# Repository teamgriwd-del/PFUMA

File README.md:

# PFUMA/INGCEBO - Enterprise Agri-Health Intelligence

*pfuma* — the Shona word for wealth. For a rural family, that wealth is standing in the kraal. PFUMA/INGCEBO is the system that protects it.

PFUMA/INGCEBO is a comprehensive, enterprise-grade livestock health and management platform specifically tailored for Zimbabwean farmers and veterinarians. Built for the Zimbabwe Agricultural Show, it provides digital tools to enhance productivity, automate health compliance, and provide rapid emergency response.

## 📊 The Problem

Livestock is often a rural family's largest store of wealth. It is also the least protected asset they own.

- **500,000+** cattle lost to disease (Theileriosis / "January Disease") since 2016 — most of it preventable if caught early.
- **3,400+** arrests in a single stock-theft crackdown operation.
- **0** verifiable digital records — police can't clear a sale they have no visibility into, and a buyer can't check a story he's only been told.
- **Paper trail, not a real one.** Ownership, health history, vaccination records and past sales are tracked on paper, by memory, or not at all — a record that can be lost, forged, or simply never existed in the first place.
- **No way to verify livestock history.** A buyer has no way to confirm an animal's health record, vaccination status, or true ownership before paying — they're trusting a stranger's word, not a record.
- **Ownership disputes with no evidence.** If a cow is stolen or its ownership is disputed, a farmer has no fast, credible way to prove it's really his.
- **Informal, undocumented sales channels.** Farmers relying on word-of-mouth buyers get lowballed with no visibility into fair market price, and have no documented sale history to fall back on.
- **Livestock wealth is illiquid.** Without verified ownership and health records, that wealth is hard to use as proof of value when a farmer needs credit.

The gap isn't goodwill — it's proof.

## 👑 The PFUMA/INGCEBO Experience

### 1. Jinda: The AI Farm Assistant
A state-of-the-art AI assistant trained on a vast knowledge base of Zimbabwean livestock protocols.
- **NLP Engine:** Handles natural language queries from non-technical users.
- **Smart Navigation:** Responds to commands like "Take me to the marketplace" or "Take me home."
- **Deep Knowledge:** Trained on January Disease (Theileriosis), Anthrax, and Cattle Gestation/Weaning standards.
- **Herd Analytics:** Instantly calculates herd size and health trends via chat.

### 2. Enterprise Diagnostics (Weighted Engine)
Advanced diagnostic system with weighted symptom matching.
- **Weighted Logic:** Differentiates between Primary and Secondary symptoms.
- **Action Plans:** Provides multi-step procedures for commercial farm management.
- **Zim Focus:** Specific training on regional threats common in Mashonaland, Matabeleland, and Midlands.

### 3. Health & Compliance (Lifecycle Engine)
A full-lifecycle system ensuring commercial compliance.
- **Automated Lifecycle:** Real-time countdowns for weaning and gestation.
- **Digital Audit Log:** Permanent, timestamped records of every vaccination and treatment.
- **Compliance Tracking:** Color-coded status for Overdue, Due Today, and Upcoming tasks.

### 4. Veterinary Advisory Portal
Structured ticketing system localized for Zimbabwe.
- **Regional Surveillance:** Location tagging by Province and District for national disease tracking.
- **Direct Hotlines:** Instant access to Department of Veterinary Services (DVS) regional offices.

### 5. Police Oversight & Sale Clearance
A fifth stakeholder role modelling real-world livestock-trade law enforcement.
- **Signup Verification Queue:** Police review Farmer/Supplier/Buyer applications (Vets are peer-reviewed by an existing verified vet); Police accounts are provisioned out-of-band, not self-service.
- **Sale Clearance Queue:** Every livestock marketplace listing tied to a registered animal starts `pending_clearance` and stays invisible to buyers until an officer verifies ownership/brand papers and issues a movement permit number.
- **Document Verification at Signup:** Every role uploads an ID document plus a role-specific credential (DVS license, business registration, land proof, etc.) — see [`signup-verification-requirements.md`](DOCUMENTATION/compliance-research/signup-verification-requirements.md).

### 6. Compliance Knowledge Base
Researched, cited reference material — not legal advice — covering Zimbabwean livestock law and species-specific health requirements for Cattle, Pigs, Sheep, and Goats. See the [`DOCUMENTATION/compliance-research/`](DOCUMENTATION/compliance-research/) folder. Jinda draws on a condensed version of this to answer "what do I need to legally keep/sell X" questions in-chat.

### 7. Real Authentication & Role-Based Access Control
- **Password auth (bcrypt) + JWT sessions** — no endpoint is open to an unauthenticated caller except health-check, login, register, and public feed reference data.
- **Per-owner data scoping** — a Farmer only ever sees their own animals/health records/inventory; Vets and Police get oversight visibility; the AI companion is role-aware and refuses to discuss another user's data.
- **Uploaded documents** are stored outside the web root and served only to the document's owner or an authorized reviewer.

### 8. Agri Marketplace
Livestock, feed, medicine and equipment listings in one feed.
- **Verified suppliers only** — feed, medicine and vaccine listings come from suppliers vetted at signup.
- **Livestock listings gated by clearance** — an animal-backed listing stays `pending_clearance` and invisible to buyers until police verify ownership/brand papers.
- Buyers see a record, not a stranger's word — the vet's health note and the police clearance travel with the sale.

### 9. PFUMA/INGCEBO Messenger
Direct in-app chat connecting every role — farmers, vets, suppliers and buyers — across Zimbabwe, filterable by role (Vets / Suppliers / Farmers / Buyers) so a farmer can go straight to the DVS officer or supplier they need instead of a phone call and a guess.

### 10. Institutions — Turning Livestock Into Usable Collateral
A sixth stakeholder role for banks and insurers.
- **Certificate Lookup:** An Institution enters a valuation certificate code (issued by a vet for a specific animal) and instantly sees a verified record — identity, health history, estimated market value — instead of taking a borrower's word for what their herd is worth.
- **Collateral/Insurance Flagging:** The Institution can flag a certificate in its own private ledger for loan-collateral or insurance-underwriting purposes, and keeps a running record of every certificate it has looked up.
- This is what makes "livestock wealth is easier to borrow against" (see below) a real, working feature rather than just a talking point.

### 11. Farmer Cooperatives
Farmers can form or join a cooperative to coordinate as a group rather than individually — a shared dip-tank schedule visible to every member, and group vet-consultation requests raised on the cooperative's behalf instead of each farmer messaging separately.

### 12. National Outbreak Reporting
Any Farmer or Veterinarian can report a suspected disease outbreak. A Veterinarian or Admin verifies it, and verification automatically broadcasts a notification to farmers in the affected area — turning informal "have you heard..." warnings into a real, timestamped, region-scoped alert system that feeds the same regional surveillance picture DVS needs for contact tracing.

## 🐄 The Journey of One Animal

| Step | What happens |
|---|---|
| **1. Register** | The farmer records breed, weight, tag ID, brand mark and dip-tank details. No brand on record is flagged as a risk before any sale. |
| **2. Track** | Weight, vaccinations, weaning and gestation run on countdowns. Overdue, due-today and upcoming are colour-coded, not remembered. |
| **3. Treat** | The farmer messages a vet in-app. The vet reviews, treats, and can order medicine from a supplier — three roles, one system. |
| **4. Clear** | The listing opens as `pending_clearance`. An officer verifies ownership and brand papers and issues a movement-permit number. |
| **5. Sell** | Only now can buyers see it. The vet's health record and the police clearance travel with the sale. |

**The headline feature:** the sale cannot go live until an officer clears it. That gate lives in the software, not in a policy document — which is exactly why it doesn't get skipped.

Every registered animal also gets a **Health Passport** — verified digital pedigree and medical record, photos, identity details (name, ear tag, owner brand, breed, age/species), and an **estimated market value** computed from weight, species and health-record history.

## ⚖️ Built on Zimbabwean Law

Every headline feature maps to a specific Act — researched, cited, and in the repo ([`DOCUMENTATION/compliance-research/`](DOCUMENTATION/compliance-research/)) for anyone who wants to check it. This is researched and cited, not a lawyer-certified audit; sources are ZimLII, FAOLEX, CVSZ, Veritas and the Consumer Council, and where a detail couldn't be confirmed, the research says so plainly instead of guessing.

| What PFUMA/INGCEBO enforces | The law it operationalizes |
|---|---|
| Listings start `pending_clearance`; an officer verifies ownership and brand papers and issues a movement-permit number | Stock Theft Prevention Act [9:18] |
| Vet signup requires a CVSZ registration number, peer-reviewed by an already-verified vet | Veterinary Surgeons Act [27:15] |
| Animal records capture brand mark, tag ID and dip-tank; "no brand on record" is flagged before a sale | Brands Act + Livestock Identification Regs |
| Jinda pushes toward DVS or police reporting when a notifiable-disease pattern appears | Animal Health Act [19:01] |
| Cross-district sales prompt for a DVS veterinary movement permit alongside police clearance | The "two-gate" movement process |
| Buyer signup requires acknowledging disclosure, fixed pricing and the statutory right of return | Consumer Protection Act [14:44] |

## 🌾 What This Changes

| For | The change |
|---|---|
| **The Farmer** | Ownership he can prove, disease caught early, and a fair, documented sales channel instead of an isolated lowball offer. Cooperatives let neighbouring farmers coordinate dip-tank schedules and vet requests as a group. |
| **The Veterinarian** | Fewer wasted trips and real outbreak visibility. Province and district tagging, plus the verified outbreak-reporting workflow, builds exactly the regional surveillance data DVS needs for contact tracing. |
| **Suppliers and Buyers** | A direct channel to the farmers who need their stock, and buyers who are no longer one bad purchase away from a receiving-stolen-goods charge. |
| **Police and DVS** | Clearance stops being a paper courtesy and becomes a structural gate. Officers review from a queue instead of chasing paperwork on foot. |
| **Banks and Insurers** | A verified certificate lookup replaces "trust the borrower" with a real record — livestock wealth becomes usable collateral, not just a claim on a loan application. |
| **The Country** | Fewer disease deaths, less theft, better price discovery and easier access to credit compound into real rural household income — a measurable outcome, not a technology showcase. |

## 🛠️ Technical Stack
- **Frontend:** React (Vite) + Tailwind CSS v4
- **Backend:** Flask + PyMySQL, bcrypt password hashing, PyJWT sessions
- **Visualization:** Recharts (Historical Trends & Herd Analytics)
- **Intelligence:** Custom NLP Logic (Jinda Engine), role-aware, sourced from `DOCUMENTATION/compliance-research/`

## 🚀 Running Locally

The whole stack launches from **`run_project.bat`** (double-click it, or run it from a terminal in this folder). It starts the database, backend, web frontend, and Expo mobile app in separate windows.

### One-time setup
1. **Install backend Python deps:** `py -m pip install -r backend\requirements.txt`
2. **Install web deps (root):** `npm install`
3. **Install mobile deps (`app\`):** `cd app && npm install`
4. **Database:** MySQL/MariaDB comes from **XAMPP** (`C:\xampp\mysql`). The schema is created automatically the first time by loading `backend\schema.sql`:
   ```
   "C:\xampp\mysql\bin\mysql.exe" -u root < backend\schema.sql
   ```
   This creates the `pfuma` database (user `root`, empty password — matches `get_db()` in `backend/app.py`).

### Connecting the phone (Expo) to the backend — IMPORTANT
The mobile app talks to Flask over Wi-Fi, so two things must be right or you'll get **"Could not reach the PFUMA/INGCEBO API. Check that Flask is running and API in config.js points to your PC's IP":**

1. **`app\config.js` → `API`** must be set to *this PC's current Wi-Fi IPv4*, e.g. `http://192.168.2.32:5000`. Find it by running `ipconfig` (the `.bat` also prints it on launch). **This changes when you switch networks** — update that one line when it does.
2. **Flask must listen on all interfaces.** `backend/app.py` runs `app.run(host='0.0.0.0', ...)` — do not change it back to the default `127.0.0.1`, or only the PC (not the phone) can reach it.
3. Phone and PC must be on the **same Wi-Fi network**, and Windows Firewall must allow Python through (allow it if prompted the first time).

### What each window is
| Window | What it runs | Address |
|--------|--------------|---------|
| PFUMA/INGCEBO MySQL | XAMPP MariaDB | localhost:3306 |
| PFUMA/INGCEBO Backend | Flask API (`py app.py`) | http://localhost:5000 |
| PFUMA/INGCEBO Frontend | Vite web dev server | (Vite prints the URL) |
| PFUMA/INGCEBO Expo | Expo mobile dev server | (scan QR in Expo Go) |

If the MySQL window says **"port in use,"** that's harmless — the database is already running.

## 📚 Documentation

Everything that isn't code lives in [`DOCUMENTATION/`](DOCUMENTATION/) — start with its [README](DOCUMENTATION/README.md). Full local setup: [`DOCUMENTATION/setup/SETUP.md`](DOCUMENTATION/setup/SETUP.md). Pitch script for the show: [`DOCUMENTATION/agric-show-2026/PITCH_GUIDE.md`](DOCUMENTATION/agric-show-2026/PITCH_GUIDE.md).

## 🌍 Target Market
Specifically designed for the **Zimbabwean agricultural landscape**, bridging the gap between traditional farming wisdom and modern enterprise technology.

**Inclusive by design:** signup accepts title deeds, 99-year leases, A1/A2 permits, and communal land allocation letters — so communal farmers are not excluded by paperwork.

---
© 2026 PFUMA/INGCEBO - Team GRIWD (Arnold T. Mapindu · Adrianny Jaliele) — Zimbabwe Agricultural Show 2026, presented with TelOne Centre for Learning

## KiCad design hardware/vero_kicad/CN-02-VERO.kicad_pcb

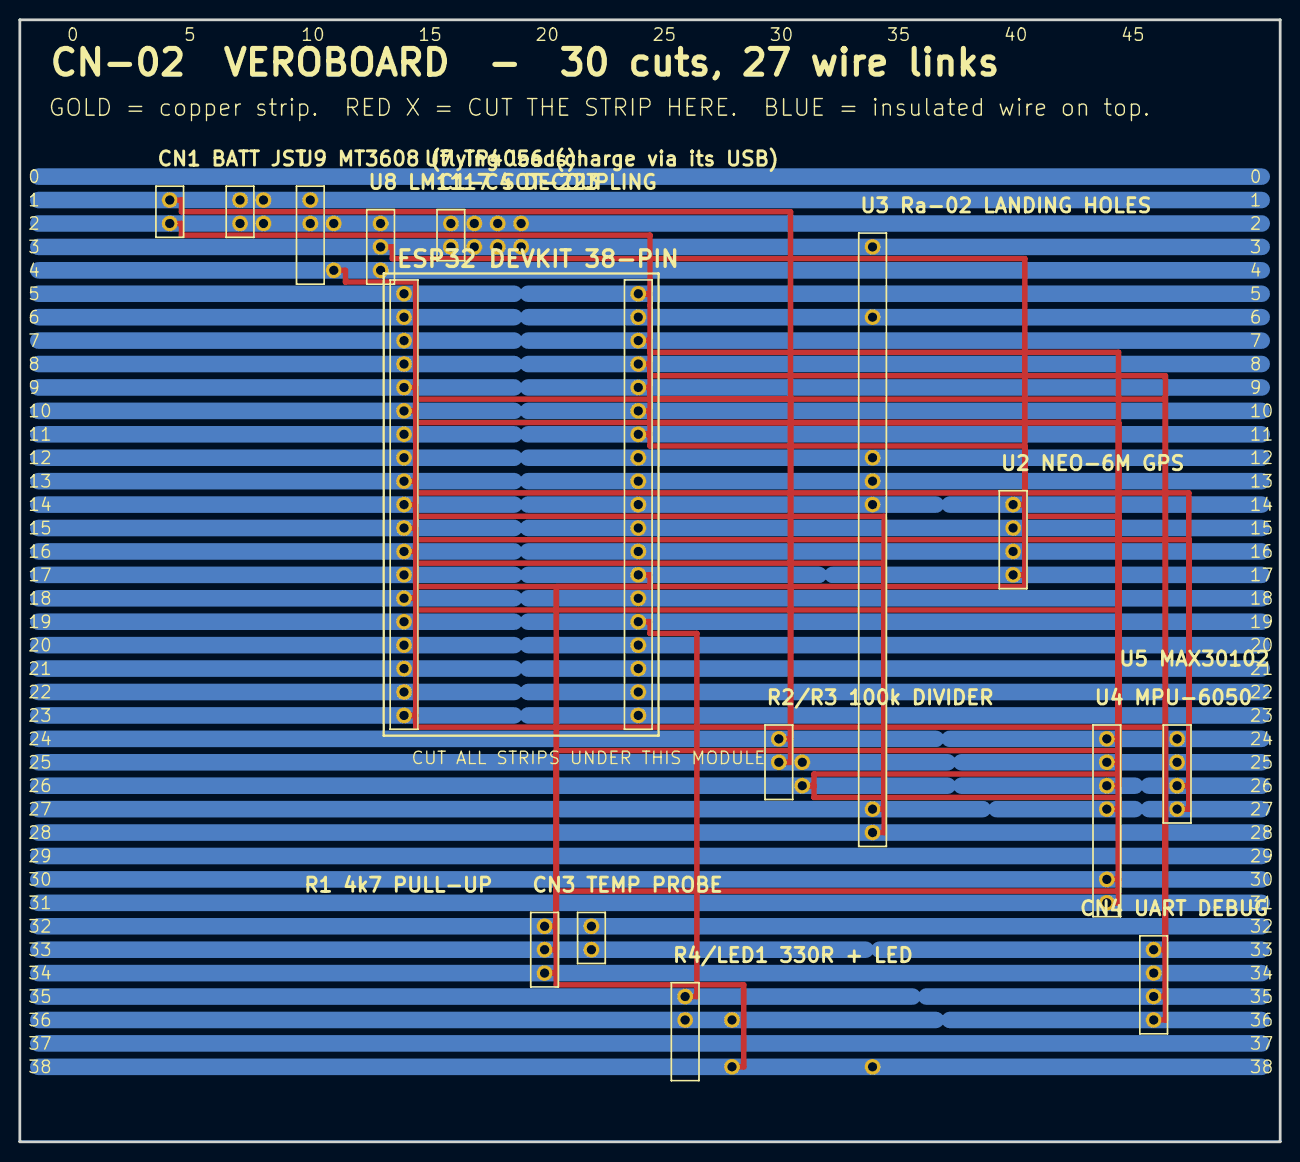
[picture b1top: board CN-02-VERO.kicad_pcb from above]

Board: 2 copper layers, 136.7 x 121.6 mm, 98 parts (0 on the bottom side), 23 nets.

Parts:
C1.1: C1.1
C1.2: C1.2
C2.1: C2.1
C2.2: C2.2
C3.1: C3.1
C3.2: C3.2
C4.1: C4.1
C4.2: C4.2
CN1.1: CN1.1
CN1.2: CN1.2
CN3.1: CN3.1
CN3.2: CN3.2
CN3.3: CN3.3
CN4.1: CN4.1
CN4.2: CN4.2
CN4.3: CN4.3
CN4.4: CN4.4
LED1.A: LED1.A
LED1.K: LED1.K
R1.1: R1.1
R1.2: R1.2
R2.1: R2.1
R2.2: R2.2
R3.1: R3.1
R3.2: R3.2
R4.1: R4.1
R4.2: R4.2
U1A.1: U1A.1
U1A.2: U1A.2
U1A.3: U1A.3
U1A.4: U1A.4
U1A.5: U1A.5
U1A.6: U1A.6
U1A.7: U1A.7
U1A.8: U1A.8
U1A.9: U1A.9
U1A.10: U1A.10
U1A.11: U1A.11
U1A.12: U1A.12
U1A.13: U1A.13
U1A.14: U1A.14
U1A.15: U1A.15
U1A.16: U1A.16
U1A.17: U1A.17
U1A.18: U1A.18
U1A.19: U1A.19
U1B.1: U1B.1
U1B.2: U1B.2
U1B.3: U1B.3
U1B.4: U1B.4
U1B.5: U1B.5
U1B.6: U1B.6
U1B.7: U1B.7
U1B.8: U1B.8
U1B.9: U1B.9
U1B.10: U1B.10
U1B.11: U1B.11
U1B.12: U1B.12
U1B.13: U1B.13
U1B.14: U1B.14
U1B.15: U1B.15
U1B.16: U1B.16
U1B.17: U1B.17
U1B.18: U1B.18
U1B.19: U1B.19
U2.1: U2.1
U2.2: U2.2
U2.3: U2.3
U2.4: U2.4
U3.DIO0: U3.DIO0
U3.GND: U3.GND
U3.MISO: U3.MISO
U3.MOSI: U3.MOSI
U3.NSS: U3.NSS
U3.RST: U3.RST
U3.SCK: U3.SCK
U3.VDD: U3.VDD
U4.1: U4.1
U4.2: U4.2
U4.3: U4.3
U4.4: U4.4
U4.7: U4.7
U4.8: U4.8
U5.1: U5.1
U5.2: U5.2
U5.3: U5.3
U5.4: U5.4
U7.B+: U7.B+
U7.B-: U7.B-
U7.OUT+: U7.OUT+
U7.OUT-: U7.OUT-
U8.1: U8.1
U8.2: U8.2
U8.3: U8.3
U9.IN+: U9.IN+
U9.IN-: U9.IN-
U9.OUT+: U9.OUT+
U9.OUT-: U9.OUT-

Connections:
+3V3: C1.2.1, C2.2.1, C3.2.1, C4.2.1, CN3.1.1, R1.1.1, U2.1.1, U3.VDD.1, U4.1.1, U5.1.1, U8.2.1
+5V: CN4.1.1, U1A.19.1, U8.3.1, U9.OUT+.1
DS18B20: CN3.2.1, R1.2.1, U1B.13.1
GND: C1.1.1, C2.1.1, C3.1.1, C4.1.1, CN1.2.1, CN3.3.1, CN4.2.1, LED1.K.1, R3.2.1, U1A.14.1, U1B.1.1, U1B.7.1, U2.4.1, U3.GND.1, U4.2.1, U4.7.1, U5.2.1, U7.B-.1, U7.OUT-.1, U8.1.1, U9.IN-.1, U9.OUT-.1
GPS_RX: U1B.11.1, U2.2.1
GPS_TX: U1B.12.1, U2.3.1
I2C2_SCL: U1A.11.1, U5.3.1
I2C2_SDA: U1A.9.1, U5.4.1
I2C_SCL: U1B.3.1, U4.3.1
I2C_SDA: U1B.6.1, U4.4.1
K1: LED1.A.1, R4.2.1
LED1_A: R4.1.1, U1B.15.1
LORA_DIO0: U1A.10.1, U3.DIO0.1
LORA_NSS: U1B.10.1, U3.NSS.1
LORA_RST: U1A.12.1, U3.RST.1
MPU_INT: U1A.6.1, U4.8.1
RX0: CN4.3.1, U1B.5.1
SPI_MISO: U1B.8.1, U3.MISO.1
SPI_MOSI: U1B.2.1, U3.MOSI.1
SPI_SCK: U1B.9.1, U3.SCK.1
TX0: CN4.4.1, U1B.4.1
VBAT: CN1.1.1, R2.1.1, U7.B+.1, U7.OUT+.1, U9.IN+.1
VBAT_SENSE: R2.2.1, R3.1.1, U1A.5.1

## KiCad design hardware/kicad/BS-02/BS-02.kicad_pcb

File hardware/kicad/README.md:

# PFUMA/INGCEBO Rev B — KiCad single-sided PCBs

> **On hold.** The current build path is the hand-soldered stripboard version
> — see [`../VEROBOARD.md`](../VEROBOARD.md). These etched-PCB files stay valid
> and DRC-clean, but nothing here is being fabricated right now. Note the PCBs
> still carry the CN-02 solar header (CN2 / VSOL), which has been dropped from
> the veroboard build.

Real KiCad 10 boards for **BS-02** (base station) and **CN-02** (collar node),
generated from script so the layout is reproducible and reviewable.

```
kicad/
  pcbkit.py     board, footprints, nets, GND pour, save
  router.py     A* maze router (single layer, turn-penalised)
  linker.py     fits wire links on F.Cu where the bottom layer cannot resolve
  bs02.py       BS-02 board definition   (140 x 120 mm)
  cn02.py       CN-02 board definition   (150 x 140 mm)
  wirelist.py   turns the DRC report into a build sheet
  BS-02/  CN-02/    .kicad_pcb, drc.txt, WIRES_TO_FIT.txt, gerbers/
```

Regenerate (KiCad's bundled Python has `pcbnew`):

```
"%LOCALAPPDATA%\Programs\KiCad\10.0\bin\python.exe" bs02.py
```

## How to read these boards

**Single-sided.** All etched copper is on **B.Cu**. Drawn as seen from the
component side, so **mirror B.Cu horizontally** before toner transfer or
single-layer CNC. Get this wrong and every board is scrap.

**GND is the pour** plus an explicit bottom-copper tree. Pads tie in with
thermal reliefs.

**F.Cu is not etched.** It carries wire links only — insulated hookup wire
soldered on the component side. Use the F.Cu Gerber as the wiring guide, and
`WIRES_TO_FIT.txt` for the remaining connections the router could not place.

**U2 / U3 Ra-02 solders on the copper side.** It is a castellated SMD module,
so on a single-sided board it mounts on the bottom, facing the copper. All
other modules sit on the component side on 2.54 mm female headers. Each LoRa
signal is broken out to a through-hole header (J1 / J2) so it can also be
reached by a wire link.

## Design rules (chosen for DIY etching)

| | |
|---|---|
| Signal / 3V3 / power trace | 0.8 / 1.2 / 2.0 mm |
| Clearance | 0.5 mm |
| Wire links (F.Cu) | 0.4 mm |
| Drills | 1.0 mm headers, 3.2 mm mounting |
| Vias | none |

## Where the pin data came from

* GPIO assignments: `collar_node.ino` / `base_station.ino`, cross-checked
  against `HARDWARE_DESIGN.md` §1.3 / §2.3. Firmware wins where they disagree
  — the doc puts the yellow WiFi LED on GPIO5, which is already LoRa NSS.
* Ra-02 pin map: KiCad's own `Ai-Thinker-Ra-02` symbol (pin 1 GND, 15 NSS).
* ESP32 module: BOM specifies the **38-pin DevKit**, so U1 is two 1x19 headers
  on a 25.4 mm row pitch.

## Verify before you etch

1. **DevKit row pitch.** Set to 25.4 mm (`LX`, `RX` in the board script).
   DevKitC V4 boards are 22.86 mm. Measure yours; change one constant and
   re-run if it differs.
2. **Module pin order.** Every module pad row is silkscreened with its signal
   name. Check each against the printed labels on your actual breakout —
   vendors vary, especially the NEO-6M (assumed VCC, RX, TX, GND).
3. **R5 / R6 on CN-02 are DNF.** The GY-521 and MAX30102 breakouts already
   carry I2C pull-ups. Fit these only with bare sensor chips.
4. Fit the 433 MHz antenna before first power-up.

## Built to the parts actually purchased

Corrected against the Pichart invoices, not the original BOM:

| Part | Was assumed | Now |
|---|---|---|
| 3.3 V regulator | 3-pin module | bare **LM1117 SOT-223**, mounts on the copper side, broken out to J3 |
| Indicator LEDs | 5 mm | **3 mm** |
| BS-02 power inlet | PCB barrel jack | **2-pin header** — the 2.5 mm jack is panel mount, wire it in |
| Bulk capacitor | disc ceramic | **radial electrolytic** |

## Dead copper removed from CN-02

`collar_node.ino` calls `LoRa.setPins(NSS, RST, DIO0)` only, and defines no
switches and one LED. Eight nets in the Rev B card were driven by nothing:

* **LoRa DIO1 / DIO2** — defined but never read. DIO2 sat on **IO12**, a
  strapping pin: held high at reset the ESP32 selects 1.8 V flash and will not
  boot. Removed.
* **SW1-SW4** (IO33/32/25/27) — no switch code exists. Removed with CN5.
* **LED2** (IO15) — firmware defines only `PIN_LED 2`. Removed.

CN-02 is now 22 nets instead of 30, with no orphans.

## Status

Both boards pass DRC with **zero violations** — no shorts, clearance, hole or
courtyard errors. What remains is connectivity the single layer could not
close, listed per board in `WIRES_TO_FIT.txt`:

| | BS-02 | CN-02 |
|---|---|---|
| Wire links routed on F.Cu | 9 | 20 |
| Wires in `WIRES_TO_FIT.txt` | 4 | 10 |
| DRC violations | 0 | 0 |

Single-sided is the binding constraint. Two 19-pin header rows form solid
~46 mm walls that nothing can cross, so every net whose peripheral sits on the
far side must go around the ends or become a wire. A 2-layer board removes
nearly all of them at the same price from any fab — the same scripts generate it.

## Still to confirm

1. **Antenna frequency.** The invoice line reads 868 MHz; the SX1278 is a
   433 MHz part. An 868 MHz whip on 433 MHz means bad SWR, much less range and
   stress on the PA. Check the label before powering up.
2. **DevKit row pitch** — set to 25.4 mm (`LX`, `RX`). DevKitC V4 is 22.86 mm.
3. **NEO-6M pin order** — assumed VCC, RX, TX, GND. `HARDWARE_DESIGN.md` says
   VCC, GND, TX, RX. Read the silkscreen on the module you have.
4. **Battery divider** — R2/R3 are 100 k. Neither invoice shows 100 k; 10 k
   would draw about 210 uA continuously off the collar cell.
5. **ESP32 mounting** — the 4-pin right-angle sockets cannot take a devkit
   (contacts face sideways, devkit pins point down) and there are only one or
   two of them. Solder the devkit in, or buy two 1x19 straight female strips.

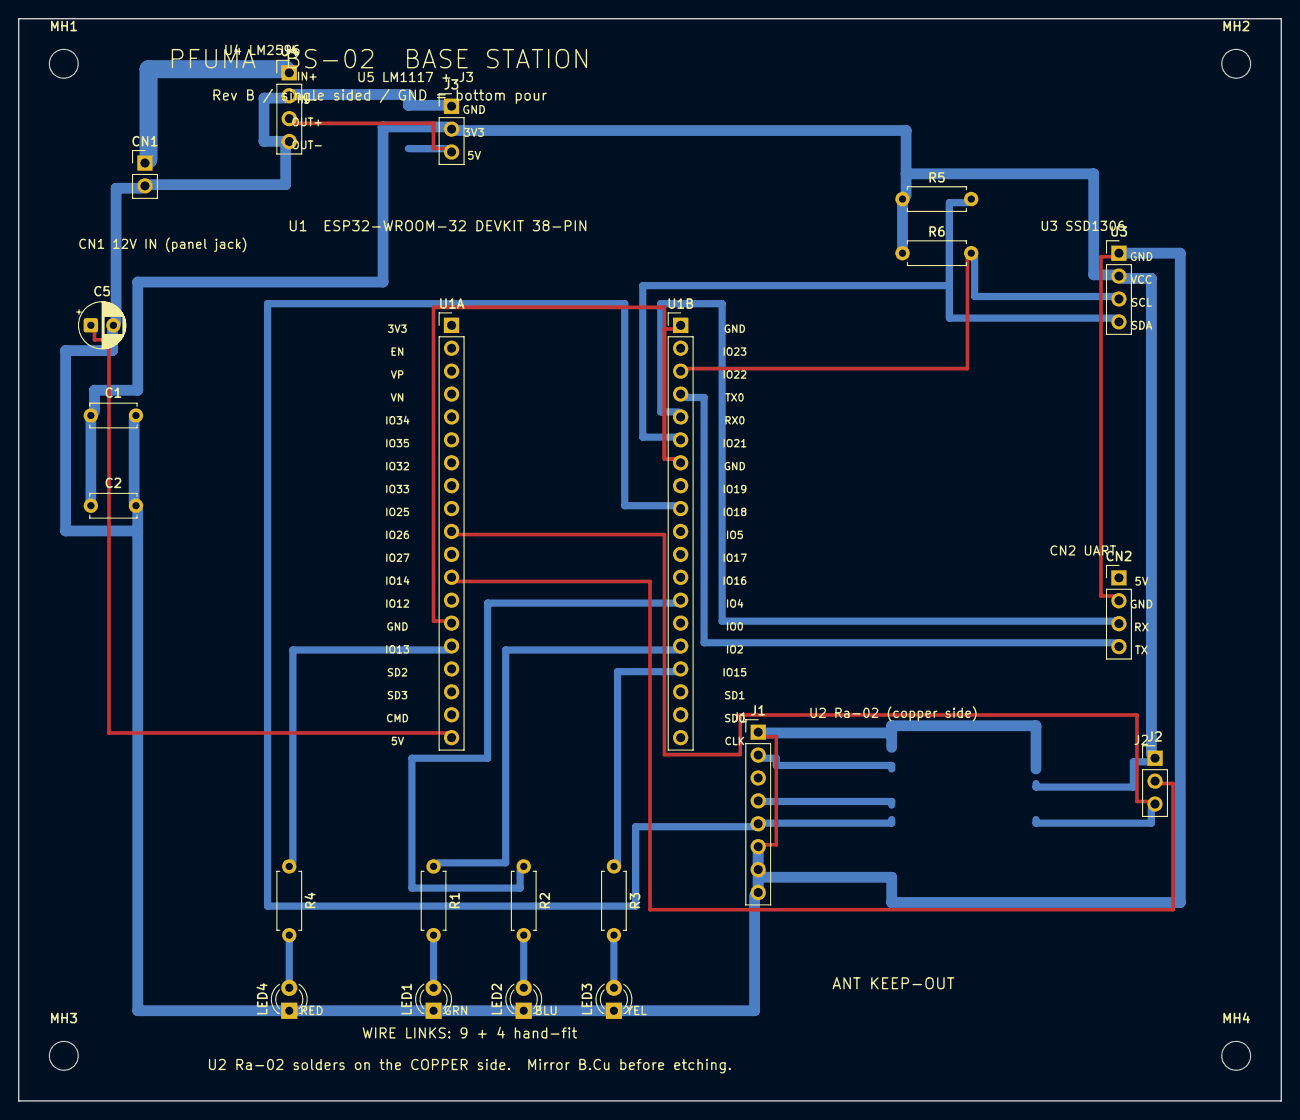
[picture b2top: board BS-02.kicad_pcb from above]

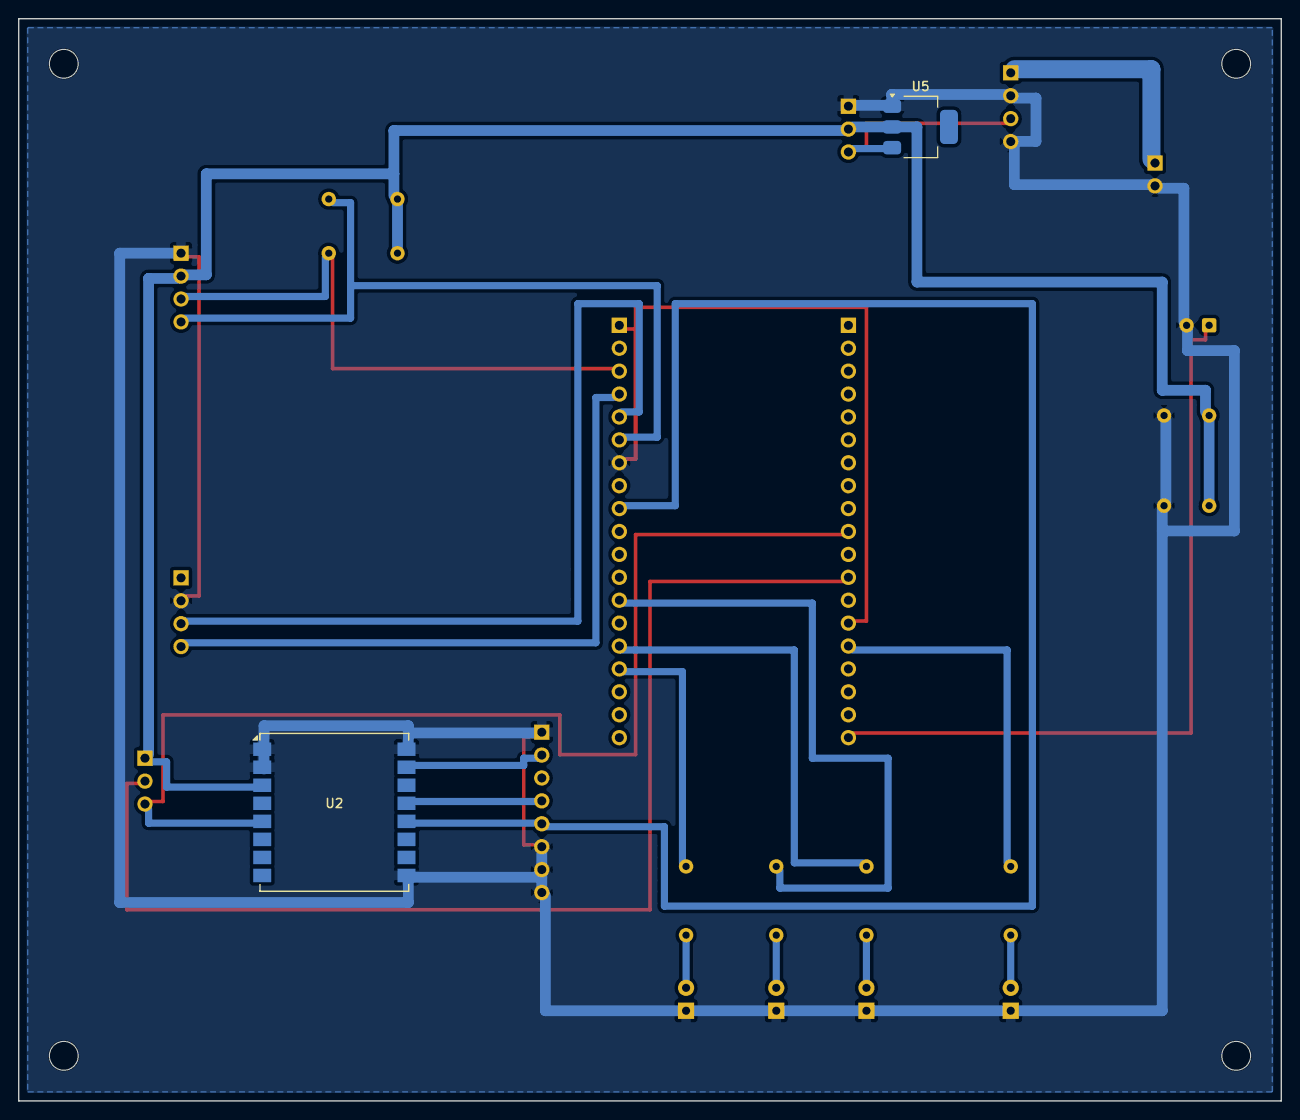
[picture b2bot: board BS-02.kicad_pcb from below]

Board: 2 copper layers, 140.0 x 120.0 mm, 28 parts (2 on the bottom side), 22 nets.

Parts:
C1, C2: 100n; C_Disc_D5.0mm_W2.5mm_P5.00mm
C5: 100u; CP_Radial_D5.0mm_P2.50mm
CN1: 12V-IN; PinHeader_1x02_P2.54mm_Vertical
CN2: UART; PinHeader_1x04_P2.54mm_Vertical
J1: LORA-SPI; PinHeader_1x08_P2.54mm_Vertical
J2: LORA-CTL; PinHeader_1x03_P2.54mm_Vertical
J3: REG; PinHeader_1x03_P2.54mm_Vertical
LED1, LED2, LED3, LED4: LED; LED_D3.0mm
MH1, MH2, MH3, MH4: M3; MountingHole_3.2mm_M3
R1, R2, R3, R4: 330R; R_Axial_DIN0207_L6.3mm_D2.5mm_P7.62mm_Horizontal
R5, R6: 4k7; R_Axial_DIN0207_L6.3mm_D2.5mm_P7.62mm_Horizontal
U1A: ESP32-L; PinHeader_1x19_P2.54mm_Vertical
U1B: ESP32-R; PinHeader_1x19_P2.54mm_Vertical
U2: Ra-02; Ai-Thinker-Ra-01-LoRa
U3: SSD1306; PinHeader_1x04_P2.54mm_Vertical
U4: LM2596; PinHeader_1x04_P2.54mm_Vertical
U5: LM1117-3.3; SOT-223-3_TabPin2

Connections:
+3V3: C1.1, C2.1, J2.1, J3.2, R5.1, R6.1, U2.3, U3.2, U5.2
+5V: C5.1, CN2.1, J3.3, U1A.19, U4.3, U5.3
+12V: CN1.1, U4.1
GND: C1.2, C2.2, C5.2, CN1.2, CN2.2, J1.1, J1.6, J1.7, J1.8, J3.1, LED1.1, LED2.1, LED3.1, LED4.1, U1A.14, U1B.1, U1B.7, U2.1, U2.2, U2.9, U2.16, U3.1, U4.2, U4.4, U5.1
I2C_SCL: R6.2, U1B.3, U3.3
I2C_SDA: R5.2, U1B.6, U3.4
K1: LED1.2, R1.2
K2: LED2.2, R2.2
K3: LED3.2, R3.2
K4: LED4.2, R4.2
LED_B: R2.1, U1B.13
LED_G: R1.1, U1B.15
LED_R: R4.1, U1A.15
LED_Y: R3.1, U1B.16
LORA_DIO0: J2.3, U1A.10, U2.5
LORA_NSS: J1.2, U1B.10, U2.15
LORA_RST: J2.2, U1A.12, U2.4
RX0: CN2.3, U1B.5
SPI_MISO: J1.4, U1B.8, U2.13
SPI_MOSI: J1.3, U1B.2, U2.14
SPI_SCK: J1.5, U1B.9, U2.12
TX0: CN2.4, U1B.4

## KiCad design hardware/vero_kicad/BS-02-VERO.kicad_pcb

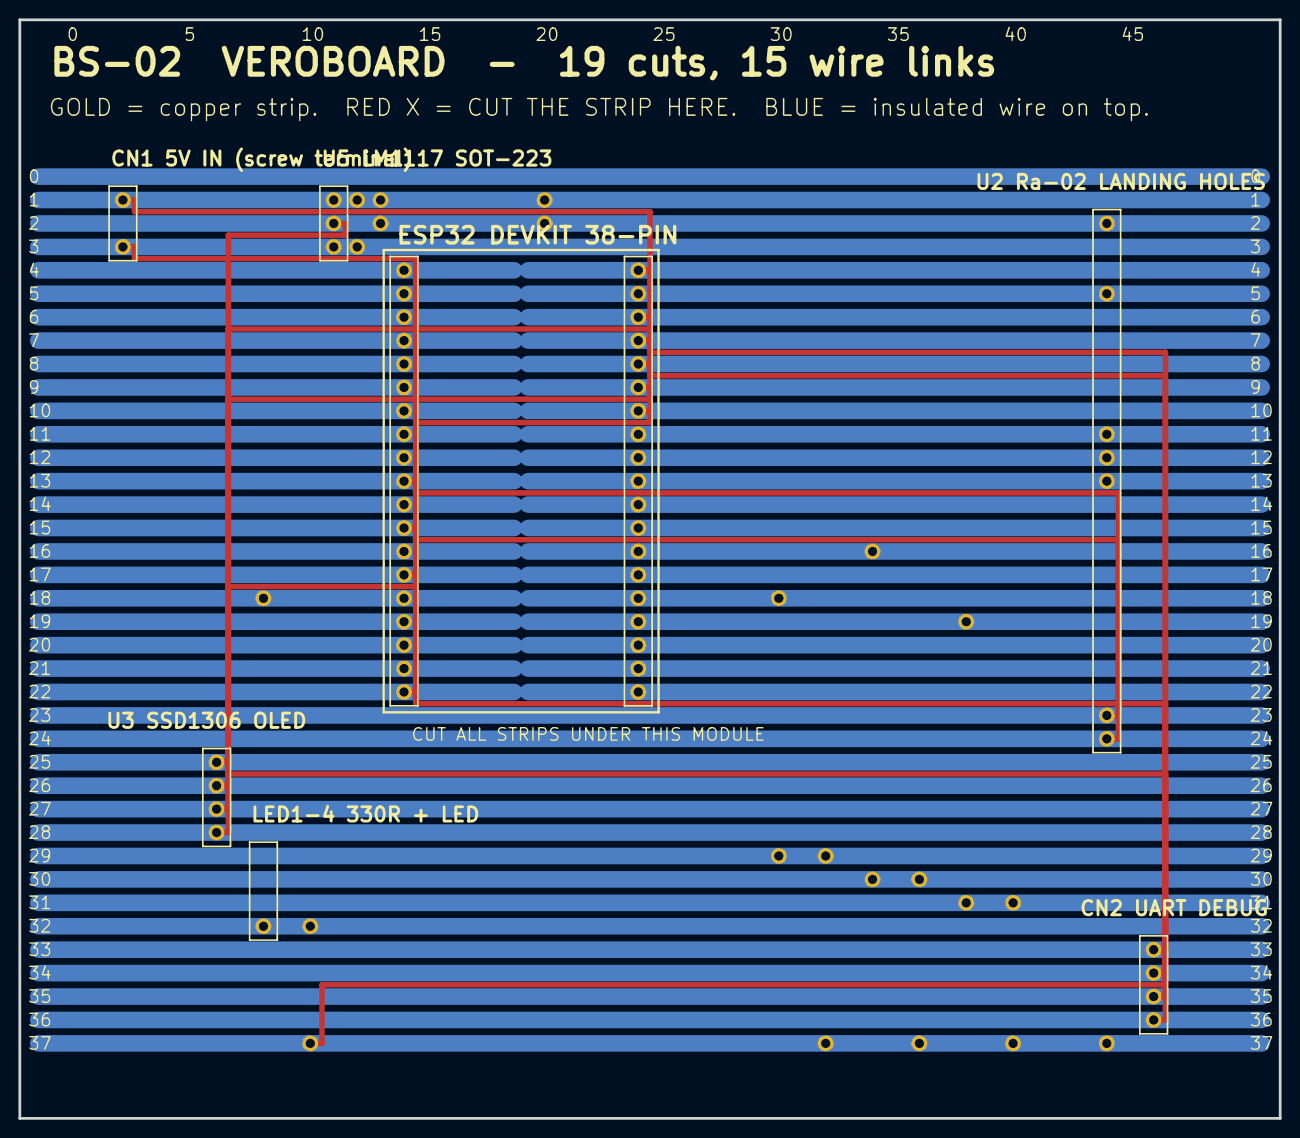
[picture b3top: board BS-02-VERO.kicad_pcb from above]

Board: 2 copper layers, 136.7 x 119.1 mm, 81 parts (0 on the bottom side), 21 nets.

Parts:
C1.1: C1.1
C1.2: C1.2
C2.1: C2.1
C2.2: C2.2
C5.1: C5.1
C5.2: C5.2
CN1.1: CN1.1
CN1.2: CN1.2
CN2.1: CN2.1
CN2.2: CN2.2
CN2.3: CN2.3
CN2.4: CN2.4
LED.K1, LED.K1#2: LED.K1
LED.K2, LED.K2#2: LED.K2
LED.K3, LED.K3#2: LED.K3
LED.K4, LED.K4#2: LED.K4
R.K1, R.K1#2: R.K1
R.K2, R.K2#2: R.K2
R.K3, R.K3#2: R.K3
R.K4, R.K4#2: R.K4
U1A.1: U1A.1
U1A.2: U1A.2
U1A.3: U1A.3
U1A.4: U1A.4
U1A.5: U1A.5
U1A.6: U1A.6
U1A.7: U1A.7
U1A.8: U1A.8
U1A.9: U1A.9
U1A.10: U1A.10
U1A.11: U1A.11
U1A.12: U1A.12
U1A.13: U1A.13
U1A.14: U1A.14
U1A.15: U1A.15
U1A.16: U1A.16
U1A.17: U1A.17
U1A.18: U1A.18
U1A.19: U1A.19
U1B.1: U1B.1
U1B.2: U1B.2
U1B.3: U1B.3
U1B.4: U1B.4
U1B.5: U1B.5
U1B.6: U1B.6
U1B.7: U1B.7
U1B.8: U1B.8
U1B.9: U1B.9
U1B.10: U1B.10
U1B.11: U1B.11
U1B.12: U1B.12
U1B.13: U1B.13
U1B.14: U1B.14
U1B.15: U1B.15
U1B.16: U1B.16
U1B.17: U1B.17
U1B.18: U1B.18
U1B.19: U1B.19
U2.DIO0: U2.DIO0
U2.GND: U2.GND
U2.MISO: U2.MISO
U2.MOSI: U2.MOSI
U2.NSS: U2.NSS
U2.RST: U2.RST
U2.SCK: U2.SCK
U2.VDD: U2.VDD
U3.1: U3.1
U3.2: U3.2
U3.3: U3.3
U3.4: U3.4
U5.1: U5.1
U5.2: U5.2
U5.3: U5.3

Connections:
+3V3: C1.2.1, C2.2.1, U2.VDD.1, U3.2.1, U5.2.1
+5V: C5.2.1, CN1.1.1, CN2.1.1, U1A.19.1, U5.3.1
GND: C1.1.1, C2.1.1, C5.1.1, CN1.2.1, CN2.2.1, LED.K1#2.1, LED.K2.1, LED.K3.1, LED.K4.1, U1A.14.1, U1B.1.1, U1B.7.1, U2.GND.1, U3.1.1, U5.1.1
I2C_SCL: U1B.3.1, U3.3.1
I2C_SDA: U1B.6.1, U3.4.1
K1: LED.K1.1, R.K1#2.1
K2: LED.K2#2.1, R.K2.1
K3: LED.K3#2.1, R.K3#2.1
K4: LED.K4#2.1, R.K4.1
LED_B: R.K2#2.1, U1B.13.1
LED_G: R.K1.1, U1B.15.1
LED_R: R.K4#2.1, U1A.15.1
LED_Y: R.K3.1, U1B.16.1
LORA_DIO0: U1A.10.1, U2.DIO0.1
LORA_NSS: U1B.10.1, U2.NSS.1
LORA_RST: U1A.12.1, U2.RST.1
RX0: CN2.3.1, U1B.5.1
SPI_MISO: U1B.8.1, U2.MISO.1
SPI_MOSI: U1B.2.1, U2.MOSI.1
SPI_SCK: U1B.9.1, U2.SCK.1
TX0: CN2.4.1, U1B.4.1

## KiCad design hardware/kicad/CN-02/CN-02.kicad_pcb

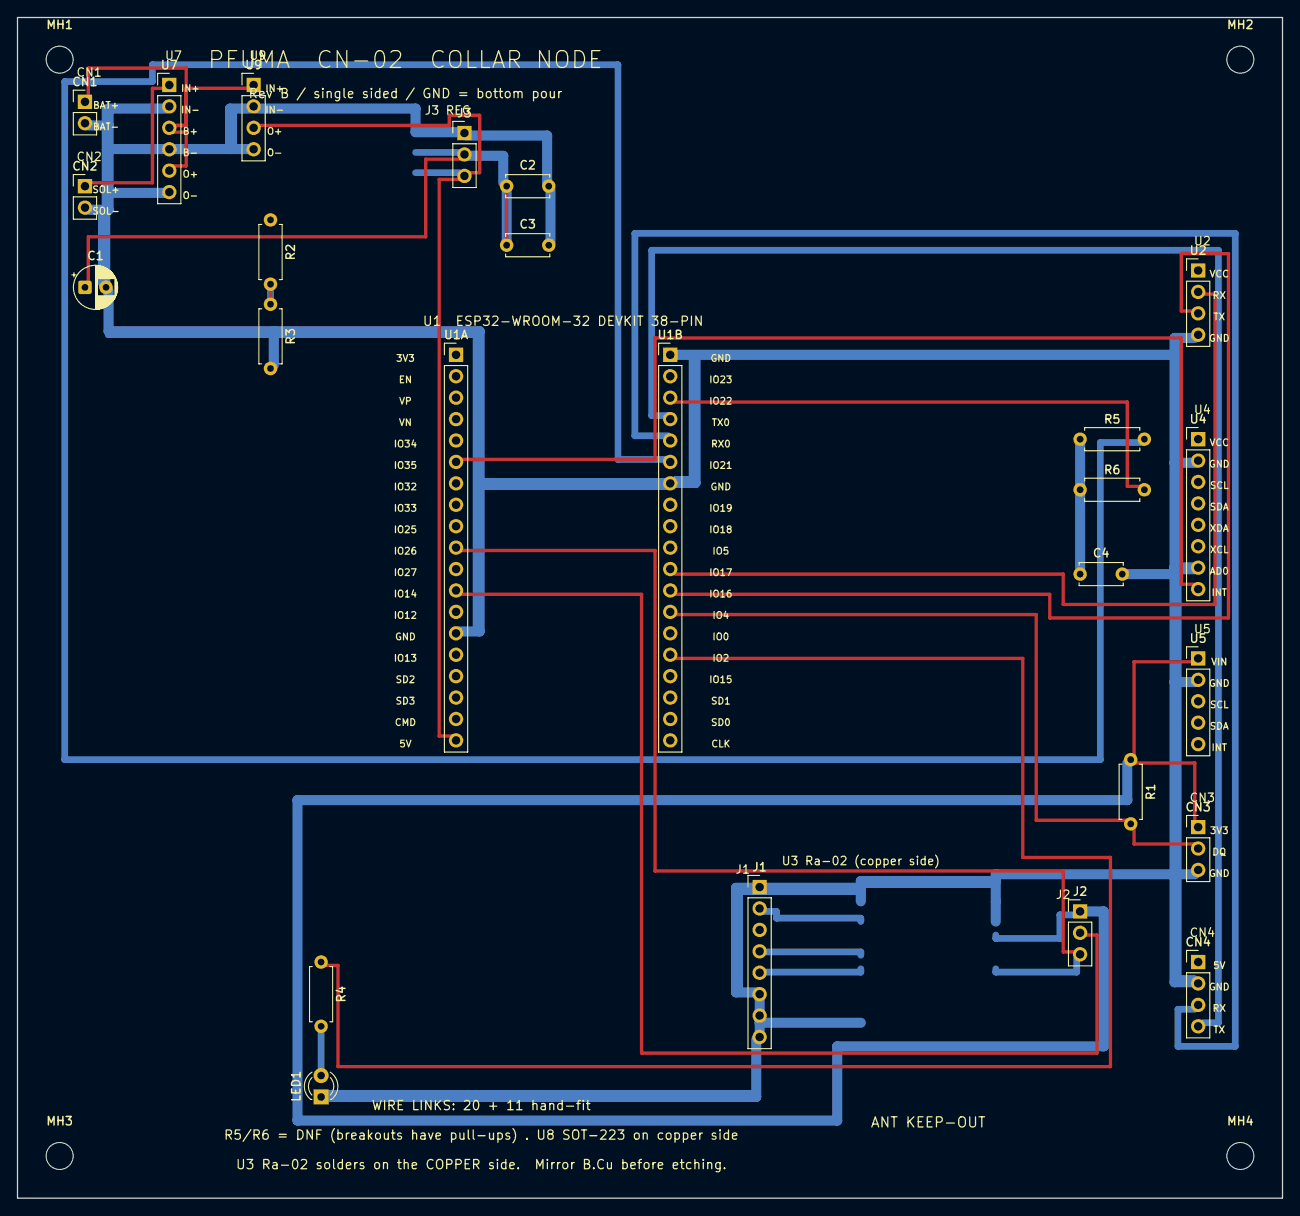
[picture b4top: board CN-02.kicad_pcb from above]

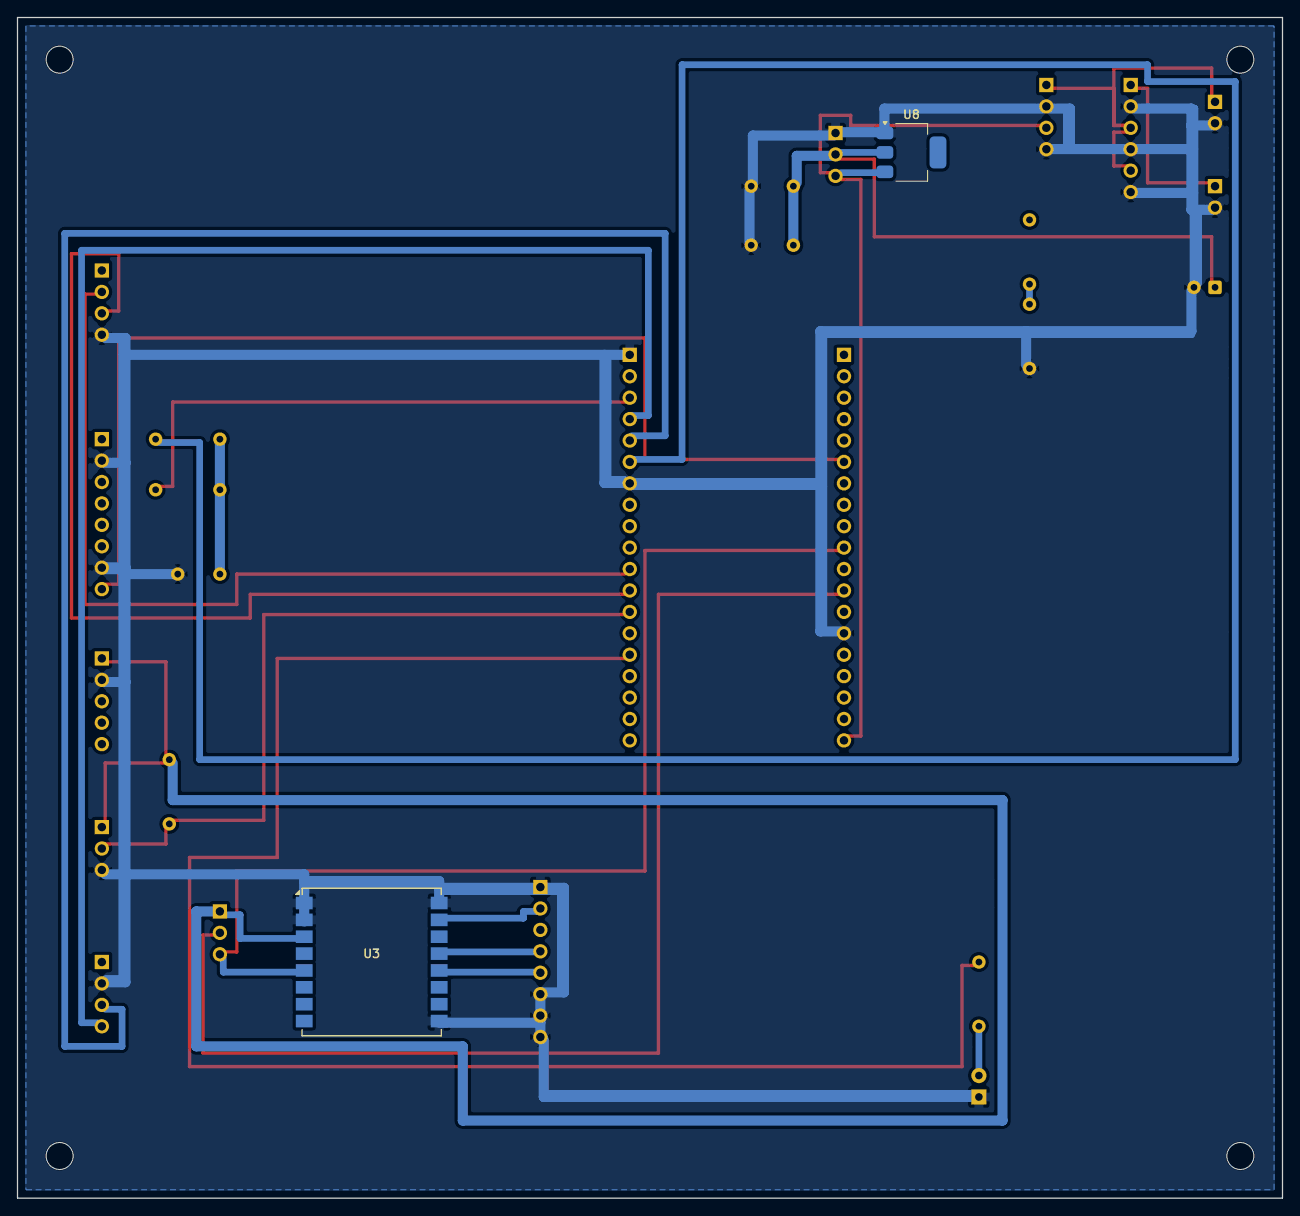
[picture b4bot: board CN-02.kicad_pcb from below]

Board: 2 copper layers, 150.0 x 140.0 mm, 31 parts (2 on the bottom side), 22 nets.

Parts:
C1: 100u; CP_Radial_D5.0mm_P2.50mm
C2, C3, C4: 100n; C_Disc_D5.0mm_W2.5mm_P5.00mm
CN1: BATT; PinHeader_1x02_P2.54mm_Vertical
CN2: SOLAR; PinHeader_1x02_P2.54mm_Vertical
CN3: TEMP; PinHeader_1x03_P2.54mm_Vertical
CN4: UART; PinHeader_1x04_P2.54mm_Vertical
J1: LORA-SPI; PinHeader_1x08_P2.54mm_Vertical
J2: LORA-CTL; PinHeader_1x03_P2.54mm_Vertical
J3: REG; PinHeader_1x03_P2.54mm_Vertical
LED1: LED; LED_D3.0mm
MH1, MH2, MH3, MH4: M3; MountingHole_3.2mm_M3
R1: 4k7; R_Axial_DIN0207_L6.3mm_D2.5mm_P7.62mm_Horizontal
R2, R3: 100k; R_Axial_DIN0207_L6.3mm_D2.5mm_P7.62mm_Horizontal
R4: 330R; R_Axial_DIN0207_L6.3mm_D2.5mm_P7.62mm_Horizontal
R5, R6: 4k7-DNF; R_Axial_DIN0207_L6.3mm_D2.5mm_P7.62mm_Horizontal
U1A: ESP32-L; PinHeader_1x19_P2.54mm_Vertical
U1B: ESP32-R; PinHeader_1x19_P2.54mm_Vertical
U2: NEO-6M; PinHeader_1x04_P2.54mm_Vertical
U3: Ra-02; Ai-Thinker-Ra-01-LoRa
U4: MPU-6050; PinHeader_1x08_P2.54mm_Vertical
U5: MAX30102; PinHeader_1x05_P2.54mm_Vertical
U7: TP4056; PinHeader_1x06_P2.54mm_Vertical
U8: LM1117-3.3; SOT-223-3_TabPin2
U9: MT3608; PinHeader_1x04_P2.54mm_Vertical

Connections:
+3V3: C1.1, C2.1, C3.1, C4.1, CN3.1, J2.1, J3.2, R1.1, R5.1, R6.1, U2.1, U3.3, U4.1, U5.1, U8.2
+5V: CN4.1, J3.3, U1A.19, U8.3, U9.3
DS18B20: CN3.2, R1.2, U1B.13
GND: C1.2, C2.2, C3.2, C4.2, CN1.2, CN2.2, CN3.3, CN4.2, J1.1, J1.6, J1.7, J1.8, J3.1, LED1.1, R3.2, U1A.14, U1B.1, U1B.7, U2.4, U3.1, U3.2, U3.9, U3.16, U4.2, U4.7, U5.2, U7.2, U7.4, U7.6, U8.1, U9.2, U9.4
GPS_RX: U1B.11, U2.2
GPS_TX: U1B.12, U2.3
I2C_SCL: R6.2, U1B.3, U4.3, U5.3
I2C_SDA: R5.2, U1B.6, U4.4, U5.4
K1: LED1.2, R4.2
LED1_A: R4.1, U1B.15
LORA_DIO0: J2.3, U1A.10, U3.5
LORA_NSS: J1.2, U1B.10, U3.15
LORA_RST: J2.2, U1A.12, U3.4
MPU_INT: U1A.6, U4.8
RX0: CN4.3, U1B.5
SPI_MISO: J1.4, U1B.8, U3.13
SPI_MOSI: J1.3, U1B.2, U3.14
SPI_SCK: J1.5, U1B.9, U3.12
TX0: CN4.4, U1B.4
VBAT: CN1.1, R2.1, U7.3, U7.5, U9.1
VBAT_SENSE: R2.2, R3.1, U1A.5
VSOL: CN2.1, U7.1

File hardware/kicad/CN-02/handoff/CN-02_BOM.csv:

Qty,References,Value,Footprint,Mounting,Notes
1,C1,100u,CP_Radial_D5.0mm_P2.50mm,top,
3,C2 C3 C4,100n,C_Disc_D5.0mm_W2.5mm_P5.00mm,top,
1,CN1,BATT,PinHeader_1x02_P2.54mm_Vertical,top,
1,CN2,SOLAR,PinHeader_1x02_P2.54mm_Vertical,top,
1,CN3,TEMP,PinHeader_1x03_P2.54mm_Vertical,top,
1,CN4,UART,PinHeader_1x04_P2.54mm_Vertical,top,
1,J1,LORA-SPI,PinHeader_1x08_P2.54mm_Vertical,top,
1,J2,LORA-CTL,PinHeader_1x03_P2.54mm_Vertical,top,
1,J3,REG,PinHeader_1x03_P2.54mm_Vertical,top,
1,LED1,LED,LED_D3.0mm,top,
1,R1,4k7,R_Axial_DIN0207_L6.3mm_D2.5mm_P7.62mm_Horizontal,top,
2,R2 R3,100k,R_Axial_DIN0207_L6.3mm_D2.5mm_P7.62mm_Horizontal,top,
1,R4,330R,R_Axial_DIN0207_L6.3mm_D2.5mm_P7.62mm_Horizontal,top,
2,R5 R6,4k7-DNF,R_Axial_DIN0207_L6.3mm_D2.5mm_P7.62mm_Horizontal,top,DO NOT FIT - breakout modules already have I2C pull-ups
1,U1A,ESP32-L,PinHeader_1x19_P2.54mm_Vertical,top,
1,U1B,ESP32-R,PinHeader_1x19_P2.54mm_Vertical,top,
1,U2,NEO-6M,PinHeader_1x04_P2.54mm_Vertical,top,
1,U3,Ra-02,Ai-Thinker-Ra-01-LoRa,COPPER SIDE (bottom),Solders flat on the copper side. Fit antenna before power-up.
1,U4,MPU-6050,PinHeader_1x08_P2.54mm_Vertical,top,
1,U5,MAX30102,PinHeader_1x05_P2.54mm_Vertical,top,
1,U7,TP4056,PinHeader_1x06_P2.54mm_Vertical,top,
1,U8,LM1117-3.3,SOT-223-3_TabPin2,COPPER SIDE (bottom),"Bare SMD regulator, copper side. Pin1 GND, Pin2 OUT, Pin3 IN."
1,U9,MT3608,PinHeader_1x04_P2.54mm_Vertical,top,

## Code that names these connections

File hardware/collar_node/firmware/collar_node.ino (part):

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//  PIN MAP  (matches HARDWARE_DESIGN.md CN-01)
// ═══════════════════════════════════════════════════════════════════════
#define PIN_ONE_WIRE     4
#define PIN_LORA_NSS     5
#define PIN_LORA_RST    14
#define PIN_LED          2
#define PIN_GPS_RX      16
#define PIN_GPS_TX      17
#define PIN_LORA_SCK    18
#define PIN_LORA_MISO   19
#define PIN_I2C_SDA     21       // Wire  - MPU-6050
#define PIN_I2C_SCL     22
#define PIN_I2C2_SDA    25       // Wire1 - MAX30102 (separate bus)
#define PIN_I2C2_SCL    27
#define PIN_LORA_MOSI   23
#define PIN_LORA_DIO0   26
#define PIN_VBAT_ADC    34
#define PIN_MPU_INT     35

// ═══════════════════════════════════════════════════════════════════════
//  CONFIGURATION
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  pinMode(PIN_LED, OUTPUT);
  blinkLED(3, 200);

  Wire.begin(PIN_I2C_SDA, PIN_I2C_SCL);        // MPU-6050
  Wire1.begin(PIN_I2C2_SDA, PIN_I2C2_SCL);     // MAX30102

  initLoRa();
  initTempSensor();
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// ═══════════════════════════════════════════════════════════════════════
void initLoRa() {
  Serial.print(F("[LoRa] Initialising 433 MHz... "));
  LoRa.setPins(PIN_LORA_NSS, PIN_LORA_RST, PIN_LORA_DIO0);
  SPI.begin(PIN_LORA_SCK, PIN_LORA_MISO, PIN_LORA_MOSI, PIN_LORA_NSS);

  if (!LoRa.begin(LORA_FREQ)) {
    Serial.println(F("FAILED — check wiring!"));
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
void initGPS() {
  Serial.print(F("[NEO-6M] Initialising UART2... "));
  gpsSerial.begin(9600, SERIAL_8N1, PIN_GPS_RX, PIN_GPS_TX);
  Serial.println(F("OK — waiting for fix"));
}

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
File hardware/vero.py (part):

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        v.pin(c, 2, "GND", "C%d.1" % (i + 1)); v.pin(c, 3, "+3V3", "C%d.2" % (i + 1))
    v.blocks.append(("C1-C4", "DECOUPLING", 16, 2, 3))
    # ---- battery divider (resistors stand vertically, one hole apart)
    v.pin(30, 24, "VBAT", "R2.1");  v.pin(30, 25, "VBAT_SENSE", "R2.2")
    v.pin(31, 25, "VBAT_SENSE", "R3.1"); v.pin(31, 26, "GND", "R3.2")
    v.blocks.append(("R2/R3", "100k DIVIDER", 30, 24, 26))
    # ---- LoRa: 2mm module, flying leads to these landing holes
    for r, n, t in ((3, "+3V3", "VDD"), (38, "GND", "GND"), (6, "SPI_MOSI", "MOSI"),
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    v.module("U5", 47, 24, ["+3V3", "GND", "I2C2_SCL", "I2C2_SDA"], "MAX30102")
    # ---- DS18B20 probe + its pull-up
    v.module("CN3", 20, 32, ["+3V3", "DS18B20", "GND"], "TEMP PROBE")
    v.pin(22, 32, "+3V3", "R1.1"); v.pin(22, 33, "DS18B20", "R1.2")
    v.blocks.append(("R1", "4k7 PULL-UP", 22, 32, 33))
    # ---- status LED
    v.pin(26, 35, "LED1_A", "R4.1"); v.pin(26, 36, "K1", "R4.2")
    v.pin(28, 36, "K1", "LED1.A");   v.pin(28, 38, "GND", "LED1.K")
    v.blocks.append(("R4/LED1", "330R + LED", 26, 35, 38))
    v.module("CN4", 46, 33, ["+5V", "GND", "RX0", "TX0"], "UART DEBUG")
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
